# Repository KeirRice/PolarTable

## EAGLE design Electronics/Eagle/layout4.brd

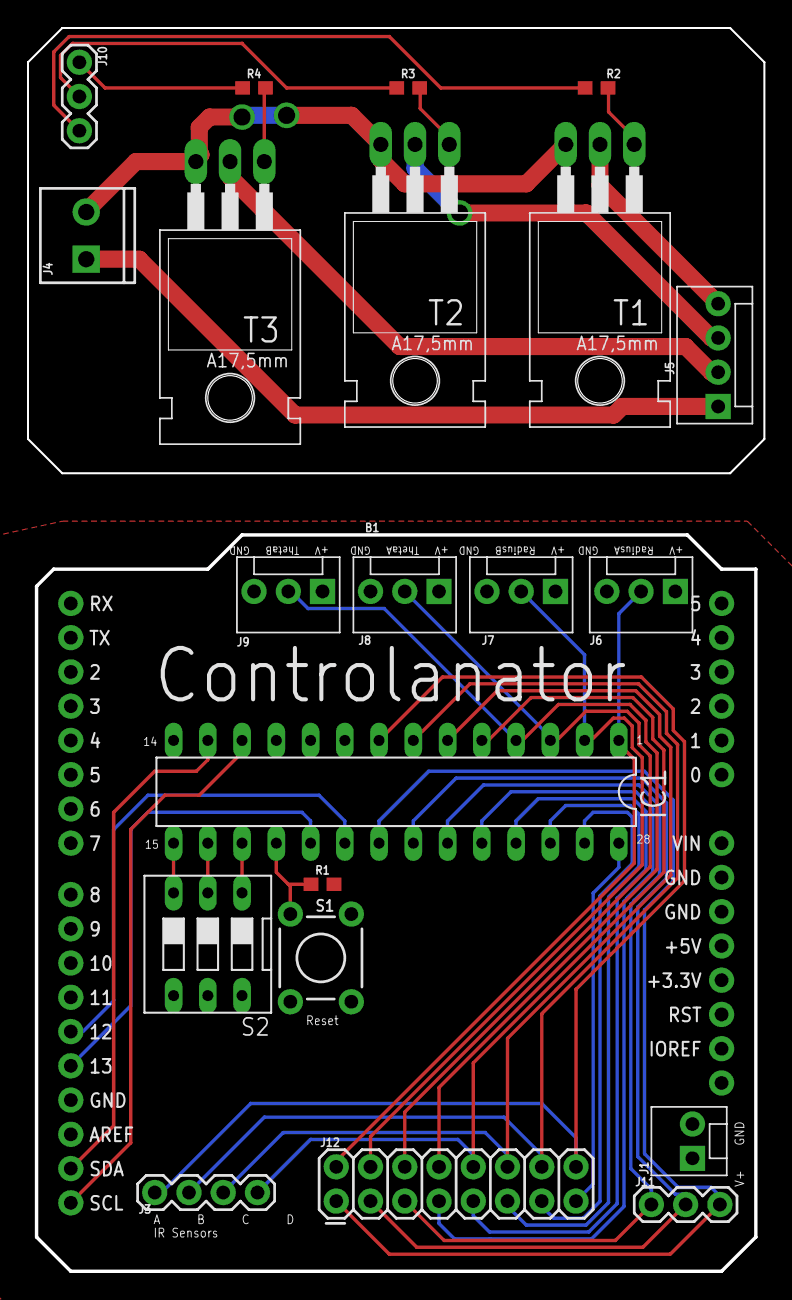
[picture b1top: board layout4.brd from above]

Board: 2 copper layers, 54.6 x 92.2 mm, 22 parts (0 on the bottom side), 37 nets.

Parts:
B1: ARDUINO_UNO_R3_SHIELDBASIC; UNO_R3_SHIELD
IC1: MCP23017SP; DIL28-3
J1: MOLEX-1X2
J3: 1X04
J4: SCREWTERMINAL-3.5MM-2
J5: LED; MOLEX-1X4
J6: Radius A; MOLEX-1X3
J7: Radius B; MOLEX-1X3
J8: Theta A; MOLEX-1X3
J9: Theta B; MOLEX-1X3
J10, J11: 1X03
J12: 2X8
R1: 10k; 0603
R2, R3, R4: 100; 0603
S1: Reset; TACTILE_SWITCH_PTH_6.0MM
S2: DS-03
T1, T2, T3: 200mA/40V; TO220

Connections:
12V: J4.1, J5.1
A0: IC1.15, S2.3
A1: IC1.16, S2.2
A2: IC1.17, S2.1
GND: B1.GND@0, B1.GND@1, B1.GND@2, IC1.10, J1.2, J6.3, J7.3, J8.3, J9.3, S1.1
GPA0: IC1.21, J11.3, J12.1
GPA1: IC1.22, J11.2, J12.3
GPA2: IC1.23, J11.1, J12.5
GPA3: IC1.24, J12.7
GPA4: IC1.25, J12.9
GPA5: IC1.26, J12.11
GPA6: IC1.27, J12.13
GPA7: IC1.28, J12.15
GPB0: IC1.1, J6.2, J12.2
GPB1: IC1.2, J7.2, J12.4
GPB2: IC1.3, J8.2, J12.6
GPB3: IC1.4, J9.2, J12.8
GPB4: IC1.5, J3.4, J12.10
GPB5: IC1.6, J3.3, J12.12
GPB6: IC1.7, J3.2, J12.14
GPB7: IC1.8, J3.1, J12.16
INT_A: B1.D12, IC1.20
INT_B: B1.D13, IC1.19
unnamed: J10.2, R3.1
unnamed: R2.2, T1.1
unnamed: J5.4, T1.2
unnamed: R3.2, T2.1
unnamed: J5.3, T2.2
unnamed: R4.2, T3.1
unnamed: J5.2, T3.2
unnamed: J4.2, T1.3, T2.3, T3.3
unnamed: J10.3, R2.1
unnamed: J10.1, R4.1
RESET: IC1.18, R1.1, S1.3
SDA: B1.SDA, IC1.13
SDL: B1.SCL, IC1.12
VCC: B1.5V, IC1.9, J1.1, J6.1, J7.1, J8.1, J9.1, R1.2, S2.4, S2.5, S2.6

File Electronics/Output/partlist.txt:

Partlist

Exported from layout4.sch at 9/8/2018 10:40 PM

EAGLE Version 9.1.3 Copyright (c) 1988-2018 Autodesk, Inc.

Assembly variant: 

Part     Value                      Device                          Package                  Library             Sheet

B1       ARDUINO_UNO_R3_SHIELDBASIC ARDUINO_UNO_R3_SHIELDBASIC      UNO_R3_SHIELD            SparkFun-Boards     1
IC1      MCP23017SP                 MCP23017SP                      DIL28-3                  adafruit            1
J1                                  CONN_02POLAR                    MOLEX-1X2                SparkFun-Connectors 1
J3                                  CONN_04                         1X04                     SparkFun-Connectors 1
J4                                  CONN_023.5MM                    SCREWTERMINAL-3.5MM-2    SparkFun-Connectors 1
J5       LED                        CONN_04POLAR                    MOLEX-1X4                SparkFun-Connectors 1
J6       Radius A                   CONN_03POLAR                    MOLEX-1X3                SparkFun-Connectors 1
J7       Radius B                   CONN_03POLAR                    MOLEX-1X3                SparkFun-Connectors 1
J8       Theta A                    CONN_03POLAR                    MOLEX-1X3                SparkFun-Connectors 1
J9       Theta B                    CONN_03POLAR                    MOLEX-1X3                SparkFun-Connectors 1
J10                                 CONN_03                         1X03                     SparkFun-Connectors 1
J11                                 CONN_03                         1X03                     SparkFun-Connectors 1
J12                                 CONN_08X2                       2X8                      SparkFun-Connectors 1
R1       10k                        10KOHM-0603-1/10W-1%            0603                     SparkFun-Resistors  1
R2       100                        100OHM-0603-1/4W-5%             0603                     SparkFun-Resistors  1
R3       100                        100OHM-0603-1/4W-5%             0603                     SparkFun-Resistors  1
R4       100                        100OHM-0603-1/4W-5%             0603                     SparkFun-Resistors  1
S1       Reset                      MOMENTARY-SWITCH-SPST-PTH-6.0MM TACTILE_SWITCH_PTH_6.0MM SparkFun-Switches   1
S2                                  DS03                            DS-03                    switch-dil          1
T1       200mA/40V                  -NPN-TO220                      TO220                    transistor-neu-to92 1
T2       200mA/40V                  -NPN-TO220                      TO220                    transistor-neu-to92 1
T3       200mA/40V                  -NPN-TO220                      TO220                    transistor-neu-to92 1

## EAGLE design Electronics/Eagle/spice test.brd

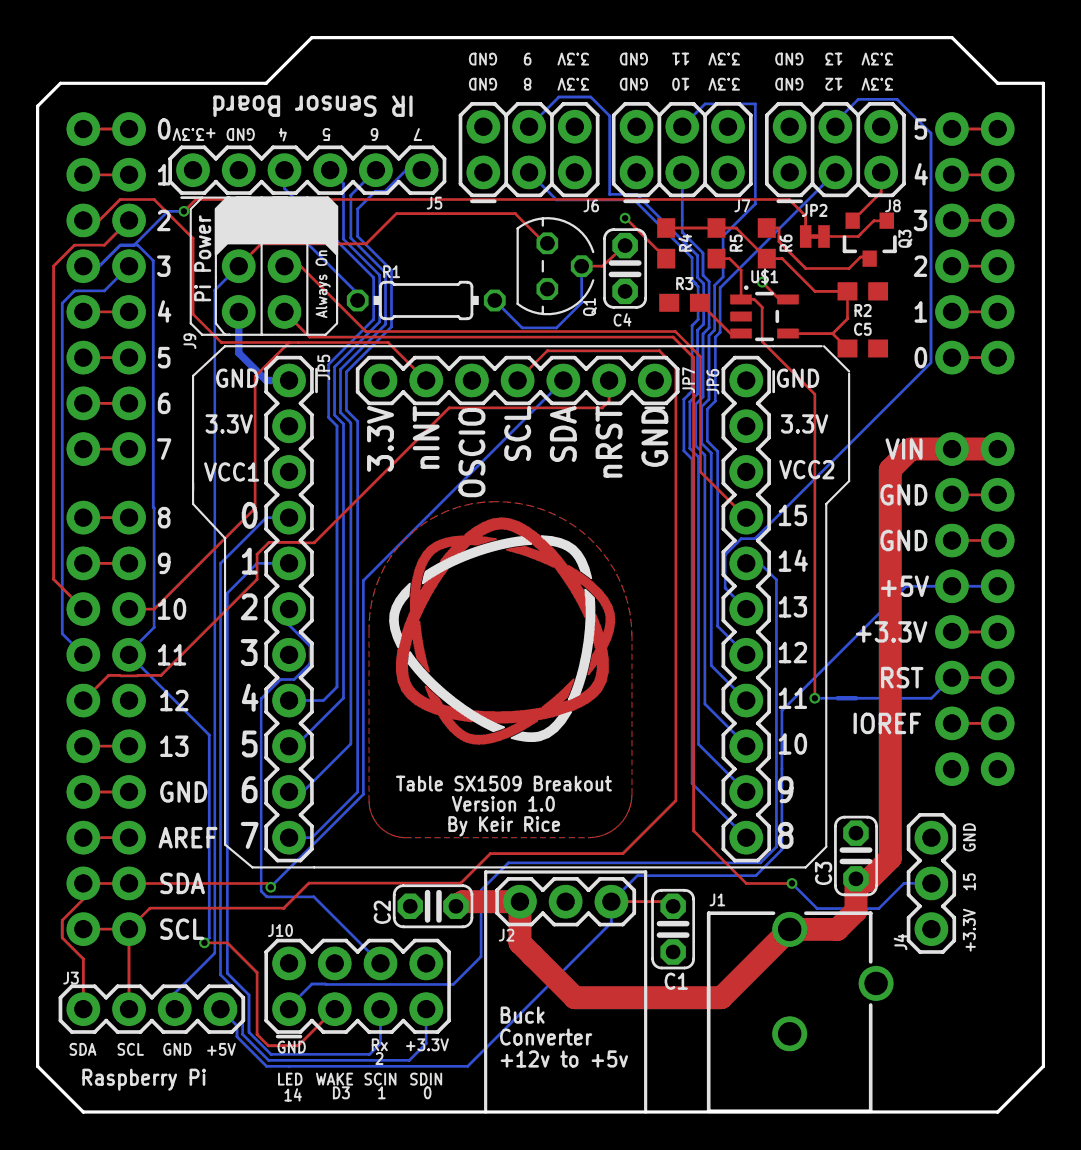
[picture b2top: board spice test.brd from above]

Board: 2 copper layers, 55.9 x 59.7 mm, 32 parts (1 on the bottom side), 53 nets.

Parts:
B1: DownConnection; UNO_R3_SHIELD_NOLABELS
B2: UpConnection; UNO_R3_SHIELD_NOLABELS
C1, C2, C3, C4: 0.1uF; C025-024X044
C5: 270PF; 0603
J1: Pi Power Jack; POWER_JACK_PTH_BREAD
J2: 12V to 5V; 1X03
J3: Pi Connection; 1X04
J4: 1X03
J5: IR Sensors; 1X06
J6: Switch A + B; 2X3
J7: Switch C + D; 2X3
J8: Switch E + F; 2X3
J9: 2X3-NS
J10: LED + Radio; 2X4
JP1, JP2: JUMPER-SMT_2_NC_TRACE_NO-SILK; SMT-JUMPER_2_NC_TRACE_NO-SILK
JP5, JP6: 1X11
JP7: 1X07
Q1: BC337; TO92
Q3: 500mA; SOT23-3
R1: 100; 0204/7
R2, R3, R4: 22k; 0603
R5: 220k; 0603
R6: 10k; 0603
U$1: OPA344; SOT23-5
U$2: TRI_LOGO_TOP_15MM

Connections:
3.3V: B1.3.3V, B2.3.3V, J4.1, J5.1, J6.5, J6.6, J7.5, J7.6, J8.5, J8.6, J10.8, JP5.2, JP6.2, JP7.7, Q3.2, R4.2, U$1.5
4: J5.3, JP5.8
5: J5.4, JP5.9
5V: B1.5V, B2.5V, C1.1, J2.3, J3.1
6: J5.5, JP5.10
7: J5.6, JP5.11
8: J6.3, JP6.11
9: J6.4, JP6.10
10: J7.3, JP6.9
10_TO_2: B1.D10, B2.D2
11: J7.4, JP6.8
11_TO_3: B1.D11, B2.D3
12: J8.3, JP6.7
12V: B1.VIN, B2.VIN, C2.2, C3.1, J1.PWR, J2.1
13: J8.4, JP6.6
14: J10.1, JP6.5
15: J9.4, JP6.4
15_PLUG: J4.2, J9.6
*D5: B1.D5, B2.D5
*D6: B1.D6, B2.D6
*D9: B1.D9, B2.D9
A0: B1.A0, B2.A0
A1: B1.A1, B2.A1
A2: B1.A2, B2.A2
A3: B1.A3, B2.A3
A4: B1.A4, B2.A4
A5: B1.A5, B2.A5
AREF: B1.AREF, B2.AREF
D4: B1.D4, B2.D4
D7: B1.D7, B2.D7
D8: B1.D8, B2.D8
D13: B1.D13, B2.D13
GND: B1.GND@0, B1.GND@1, B1.GND@2, B2.GND@0, B2.GND@1, B2.GND@2, C1.2, C2.1, C3.2, C4.2, C5.2, J1.GND, J1.GNDBREAK, J2.2, J4.3, J5.2, J6.1, J6.2, J7.1, J7.2, J8.1, J8.2, J9.5, J10.2, JP5.1, JP6.1, JP7.1, Q1.1, R2.1, R3.1, U$1.2
IOREF: B1.IOREF, B2.IOREF
unnamed: C5.1, R2.2, R4.1, R5.2, R6.2, U$1.4
unnamed: C4.1, Q1.2, R1.2
unnamed: JP2.2, Q3.1
unnamed: J9.2, R1.1
unnamed: R3.2, U$1.3
unnamed: JP1.1, R5.1, U$1.1
unnamed: Q3.3, R6.1
NINT: B1.D2, B2.D10, JP7.6
NRESET: B1.D12, JP7.2
PI_GROUND: J3.2, J9.3, Q1.3
RES: B1.RES, B2.RES, JP1.2
RX: B1.RX, B2.RX
RXDATA: J10.6, JP5.6
SCIN: J10.5, JP5.5
SCL: B1.SCL, B2.SCL, J3.3, JP7.4
SDA: B1.SDA, B2.SDA, J3.4, JP7.3
SDIN: J10.7, JP5.4
TX: B1.TX, B2.TX
WAKE_SW: B1.D3, B2.D11, J10.3, JP2.1

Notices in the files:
parts and their libraries:
SparkFun-Resistors: Licensing: Creative Commons ShareAlike 4.0 International - https://creativecommons.org/licenses/by-sa/4.0
SparkFun-Connectors: Licensing: CC v3.0 Share-Alike You are welcome to use this library for commercial purposes.
